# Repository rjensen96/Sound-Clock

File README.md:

<<<<<<< Updated upstream
# Sound-Clock
A thing where you hit it and it tells you what time it is.

Sounds provided by: https://ttsreader.com/
=======
# Esp32WavI2s
A .wav file player for the Esp32 using the Arduino IDE (and VS Code)
>>>>>>> Stashed changes

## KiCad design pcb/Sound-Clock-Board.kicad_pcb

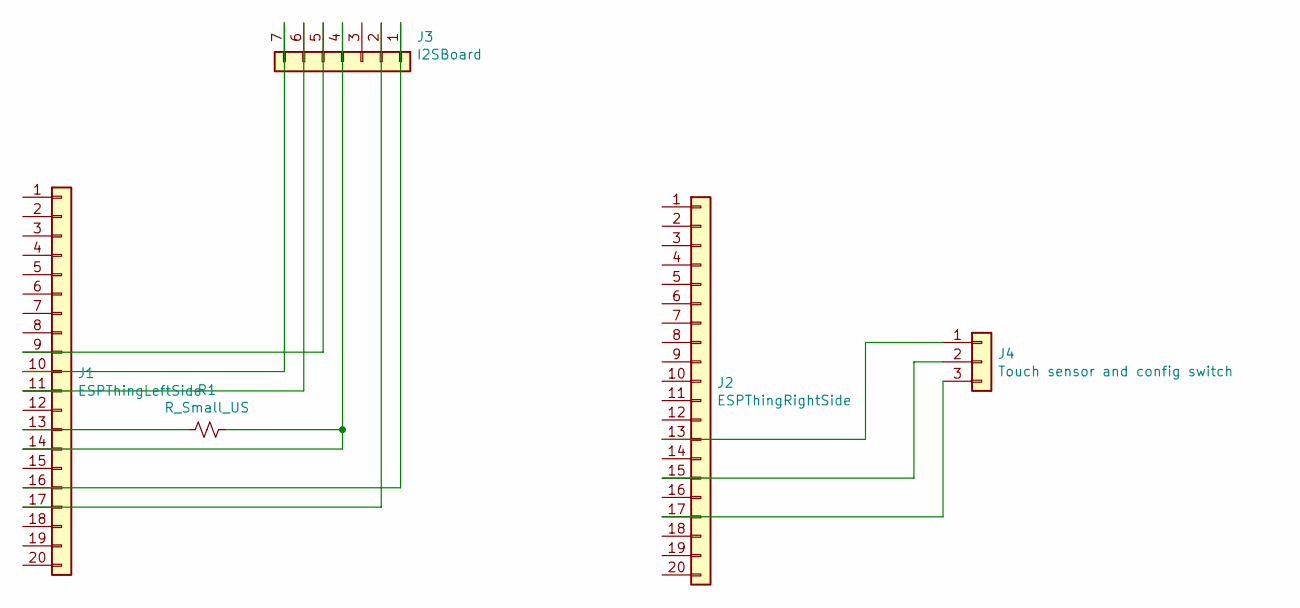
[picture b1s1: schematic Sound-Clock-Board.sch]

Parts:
J1: ESPThingLeftSide; PinHeader_1x20_P2.54mm_Vertical
J2: ESPThingRightSide; PinHeader_1x20_P2.54mm_Vertical
J3: I2SBoard; PinHeader_1x07_P2.54mm_Vertical
J4: Touch sensor and config switch; PinHeader_1x03_P2.54mm_Vertical
R1: R_Small_US; R_Axial_DIN0207_L6.3mm_D2.5mm_P2.54mm_Vertical

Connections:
unnamed: J1.9, J3.5
unnamed: J1.10, J3.7
unnamed: J1.11, J3.6
unnamed: J1.13, R1.2
unnamed: J1.14, J3.4, R1.1
unnamed: J1.16, J3.1
unnamed: J1.17, J3.2
unnamed: J2.13, J4.1
unnamed: J2.15, J4.2
unnamed: J2.17, J4.3

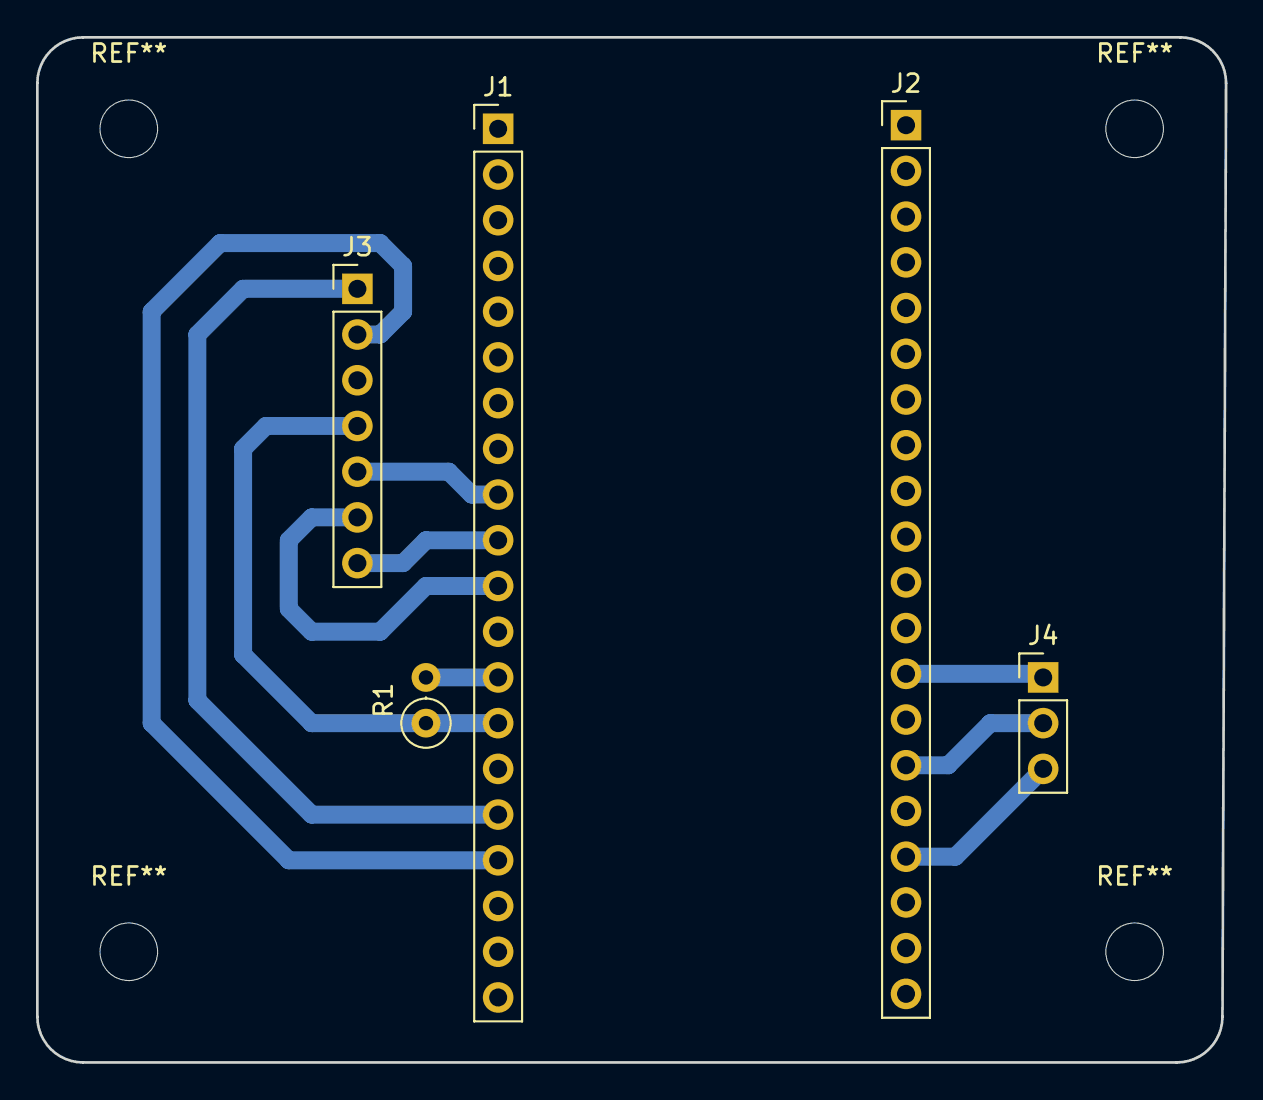
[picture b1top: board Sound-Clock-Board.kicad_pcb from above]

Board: 2 copper layers, 66.0 x 57.0 mm, 5 parts (0 on the bottom side), 10 nets.

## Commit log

2020-11-17 initial upload
    code is still the GrowLight stuff, not anything to do with SoundClock yet.
2020-11-25 Added Sound Captures
    Sound recordings in the sound folder. Tried to get these as small as possible... we will see if it works. Worst case scenario I get to redo 50 minutes of grunt labor!! YEEHAW
2020-11-27 Added the PCB
2020-11-28 Updates to loop() and setup()
    Updated logic for loop and setup. Current state never stops saying the minute and repeats hour every 10 seconds.
2020-11-28 Resolved conflicts in sound .h files
    Made everything a `const` again. There may still be issues with the #include paths
2020-11-28 Updated the pcb and the gcode files because the origin was wrong.
2020-11-28 Deleted the Copy1127.ino file because it was actually just a copy of our main ino file. It just caused a lot of compiler errors because it got included too!
2020-12-01 Update Sound-Clock.ino
    The clock was not staying in WAITING state, it was just going directly to what sounded like SPEAK_MINUTE. In fact, it wasn't in SPEAK_MINUTE, it was going through SPEAK_HOUR so quickly that we weren'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
2020-12-01 Updated PCB.
    The radio isn't working right when it's plugged into the board, so there's a problem on this simple board somewhere.
2020-12-01 Quit printing the Wav header
    It's just a mess to look at in the logs. Wasn't actually helping to find the problem.
2020-12-03 Sound experiment
    A sound experiment - waiting long enough for the Hour speech to finish before trying to send the Minute. it worked, but I need to make the calculation real instead of hardcoded.
2020-12-03 Fixed an incorrect trace
    I had a trace going to the VBAT pin that should have been going to VUSB. Worked when not plugged in, or when in a breadboard, but didn't work on the circuit boards I milled.
2020-12-03 ++Touchplate Logic
    Added logic for controlling / sensing if the thing was touched to trigger sound.
2020-12-03 Merged Ryan's change for the touch sensor. Fixed the "oh one" problem. Mangled playback is still unfortunately a thing.
2020-12-03 Refactored the capacitive sense trigger
2020-12-03 Moved Sound-Clock into its own folder so I can make a separate folder for tests.
2020-12-03 Sound playback MUCH IMPROVED!
    This is kind of dumb, because I copied all of the samples over into the test directory, but I just want to check this in right now... it was hard to find the one thing that had to change. Biggest fac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
2020-12-04 Added gain control and merged the single pin header with the two pin header for strength
2020-12-04 Just updated a comment
2020-12-04 Updated PCB. This one works and has volume control!
2020-12-04 Code to match the new PCB. Includes a volume selector.
2020-12-05 Deleted Excess .wav and .h for sound
    Deleted files that we never plan to use. Will only speak multiples of 5 to save space.
2020-12-05 Added the configuration server and pulled out EZTime
2020-12-05 Divide by 5 so you get the right sound file.
2020-12-05 Deleted the extraneous data directory
2020-12-05 added oclock wav file
2020-12-05 new oclock at 8000hz
2020-12-05 Upchucking
2020-12-05 Added calls to update the time.
